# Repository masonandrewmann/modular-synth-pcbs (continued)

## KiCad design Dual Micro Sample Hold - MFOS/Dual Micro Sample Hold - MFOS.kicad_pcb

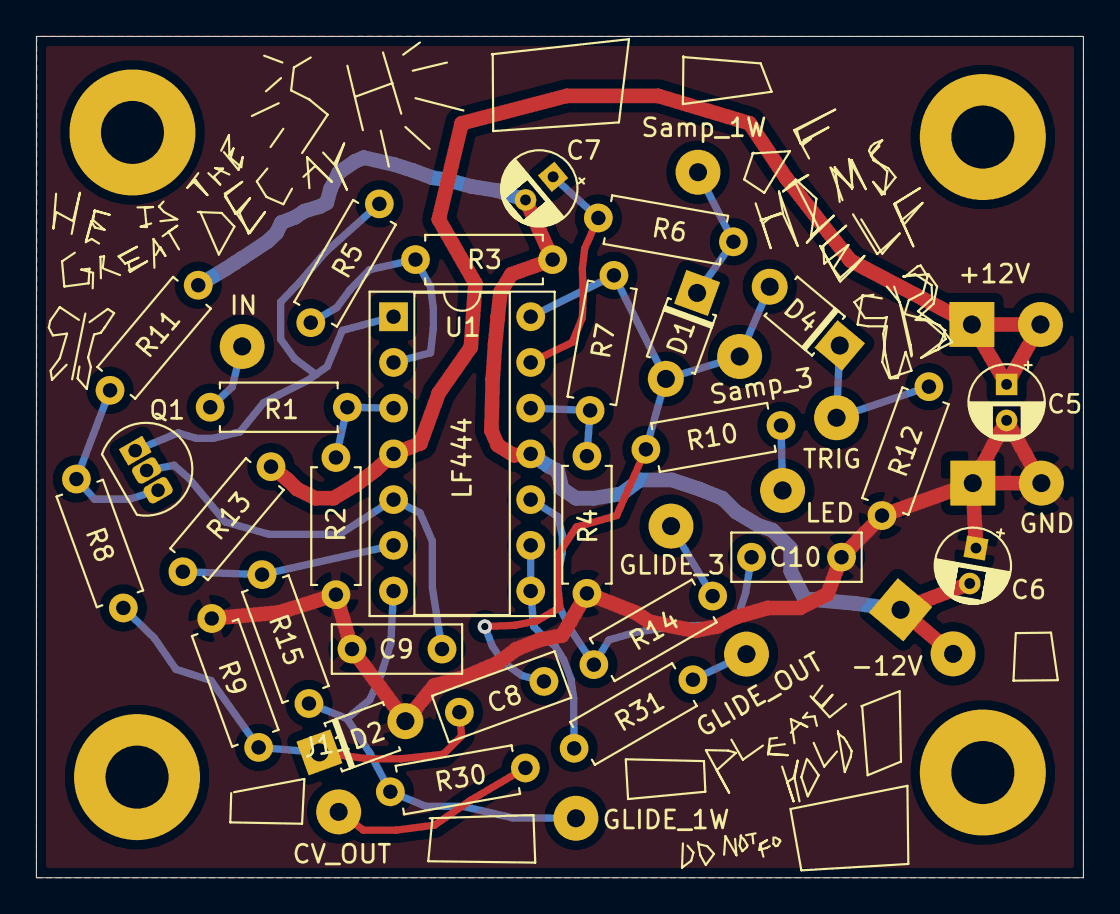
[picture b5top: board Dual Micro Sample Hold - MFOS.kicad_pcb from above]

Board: 2 copper layers, 58.2 x 46.7 mm, 40 parts (0 on the bottom side), 23 nets.

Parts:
C5, C6: 1u; CP_Radial_D4.0mm_P2.00mm
C7: 10u; CP_Radial_D4.0mm_P2.00mm
C8: 0.001u; C_Rect_L7.0mm_W2.5mm_P5.00mm
C9: 0.005u; C_Rect_L7.0mm_W2.5mm_P5.00mm
C10: 0.1u; C_Rect_L7.0mm_W2.5mm_P5.00mm
D1, D2, D4: 1N914; D_T-1_P5.08mm_Horizontal
J1: +12V_Conn; SolderWirePad_1x02_P3.81mm_Drill1mm
J2: GND_Conn; SolderWirePad_1x02_P3.81mm_Drill1mm
J3: -12V_Conn; SolderWirePad_1x02_P3.81mm_Drill1mm
J4: IN_A; SolderWirePad_1x01_Drill1mm
J5: SampRate_1W_A; SolderWirePad_1x01_Drill1mm
J6: SampRate_3_A; SolderWirePad_1x01_Drill1mm
J7: LED_A; SolderWirePad_1x01_Drill1mm
J8: Glide_1W_A; SolderWirePad_1x01_Drill1mm
J9: Glide_3_A; SolderWirePad_1x01_Drill1mm
J10: TRIG_A; SolderWirePad_1x01_Drill1mm
J11: CV_OUT_A; SolderWirePad_1x01_Drill1mm
J12: GLIDE_OUT_A; SolderWirePad_1x01_Drill1mm
Q1: Q_NJFET_DSG; TO-92L_Inline
R1, R2, R4, R8, R9: 100k; R_Axial_DIN0207_L6.3mm_D2.5mm_P7.62mm_Horizontal
R3: 560k; R_Axial_DIN0207_L6.3mm_D2.5mm_P7.62mm_Horizontal
R5: 200k; R_Axial_DIN0207_L6.3mm_D2.5mm_P7.62mm_Horizontal
R6: 4k7; R_Axial_DIN0207_L6.3mm_D2.5mm_P7.62mm_Horizontal
R7, R11: 470k; R_Axial_DIN0207_L6.3mm_D2.5mm_P7.62mm_Horizontal
R10: 10K; R_Axial_DIN0207_L6.3mm_D2.5mm_P7.62mm_Horizontal
R12: 100K; R_Axial_DIN0207_L6.3mm_D2.5mm_P7.62mm_Horizontal
R13: 150k; R_Axial_DIN0207_L6.3mm_D2.5mm_P7.62mm_Horizontal
R14: 220; R_Axial_DIN0207_L6.3mm_D2.5mm_P7.62mm_Horizontal
R15: 75k; R_Axial_DIN0207_L6.3mm_D2.5mm_P7.62mm_Horizontal
R30, R31: 1k; R_Axial_DIN0207_L6.3mm_D2.5mm_P7.62mm_Horizontal
U1: LF444; DIP-14_W7.62mm_Socket

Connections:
+12V: C5.1, J1.1, J1.2, R13.1, U1.4
-12V: C6.2, C7.2, J3.1, J3.2, R3.1, R11.2, U1.11
Earth: C5.2, C6.1, C9.2, C10.2, D2.2, J2.1, J2.2, R2.2, R4.1, R9.2, R12.2
unnamed: C7.1, R6.1, U1.13
unnamed: C8.1, D2.1, R8.1, R9.1
unnamed: C8.2, D1.2, D4.2, J6.1, R7.2, R10.1, U1.14
unnamed: C9.1, Q1.2, U1.5
unnamed: C10.1, R14.2, U1.10
unnamed: D1.1, J5.1, R6.2
unnamed: J7.1, R10.2
unnamed: D4.1, J10.1, R12.1
unnamed: J4.1, R1.1
unnamed: J8.1, R15.1, R30.1, U1.7
unnamed: J9.1, R14.1
unnamed: J11.1, R30.2
unnamed: J12.1, R31.2
unnamed: Q1.1, R5.2, U1.1
unnamed: Q1.3, R8.2, R11.1
unnamed: R1.2, R2.1, U1.3
unnamed: R3.2, R5.1, U1.2
unnamed: R4.2, R7.1, U1.12
unnamed: R13.2, R15.2, U1.6
unnamed: R31.1, U1.8, U1.9

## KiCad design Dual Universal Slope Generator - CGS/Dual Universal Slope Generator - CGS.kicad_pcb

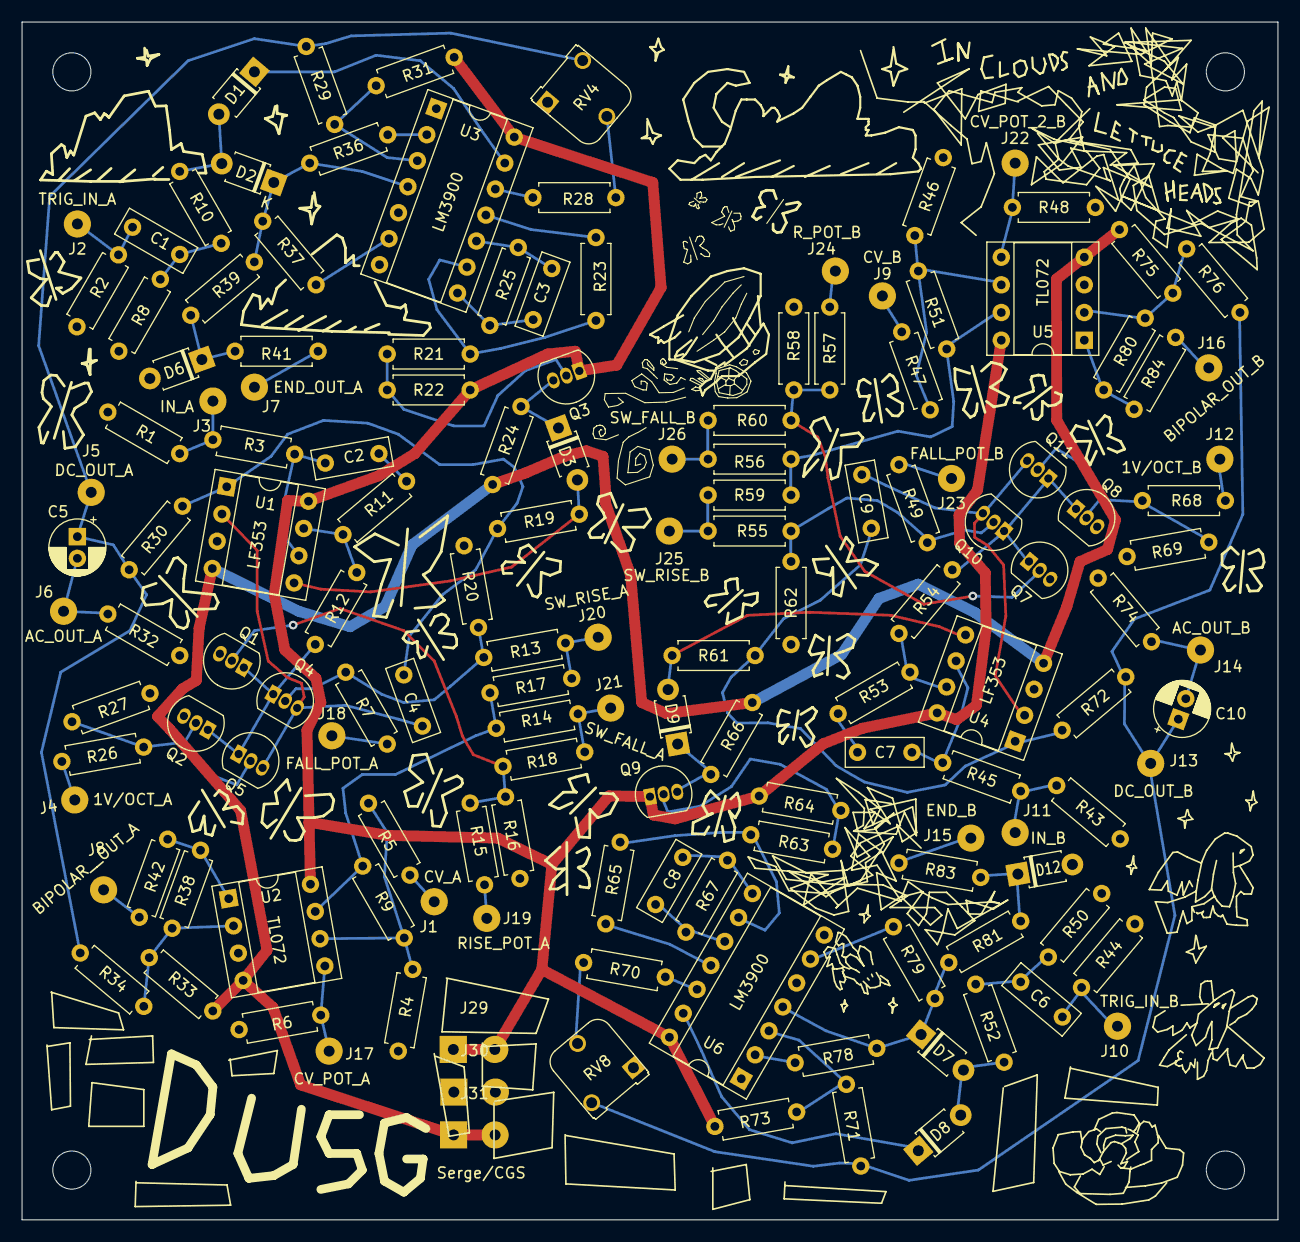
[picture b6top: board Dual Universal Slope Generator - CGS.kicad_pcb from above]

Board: 2 copper layers, 115.3 x 110.0 mm, 145 parts (0 on the bottom side), 89 nets.

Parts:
C1, C6: 1n; C_Rect_L7.0mm_W2.5mm_P5.00mm
C2, C3, C7, C8: 47p; C_Rect_L7.0mm_W2.5mm_P5.00mm
C4, C9: 22n; C_Rect_L7.0mm_W2.5mm_P5.00mm
C5, C10: 47uF; CP_Radial_D5.0mm_P2.00mm
D1, D2, D3, D7, D8, D9: 1N4148; D_T-1_P5.08mm_Horizontal
D6, D12: 5V6; D_T-1_P5.08mm_Horizontal
J1: CV_IN_A; SolderWirePad_1x01_Drill1mm
J2: TRIG_IN_A; SolderWirePad_1x01_Drill1mm
J3: IN_A; SolderWirePad_1x01_Drill1mm
J4: 1V/OCT_A; SolderWirePad_1x01_Drill1mm
J5: DC_OUT_A; SolderWirePad_1x01_Drill1mm
J6: AC_COUPLED_OUT_A; SolderWirePad_1x01_Drill1mm
J7: END_OUT_A; SolderWirePad_1x01_Drill1mm
J8: BIPOLAR_OUT_A; SolderWirePad_1x01_Drill1mm
J9: CV_IN_B; SolderWirePad_1x01_Drill1mm
J10: TRIG_IN_B; SolderWirePad_1x01_Drill1mm
J11: IN_B; SolderWirePad_1x01_Drill1mm
J12: 1V/OCT_B; SolderWirePad_1x01_Drill1mm
J13: DC_OUT_B; SolderWirePad_1x01_Drill1mm
J14: AC_COUPLED_OUT_B; SolderWirePad_1x01_Drill1mm
J15: END_OUT_B; SolderWirePad_1x01_Drill1mm
J16: BIPOLAR_OUT_B; SolderWirePad_1x01_Drill1mm
J17: CV_POT_A; SolderWirePad_1x01_Drill1mm
J18: FALL_POT_A; SolderWirePad_1x01_Drill1mm
J19: RISE_POT_A; SolderWirePad_1x01_Drill1mm
J20: SW_RISE_A; SolderWirePad_1x01_Drill1mm
J21: SW_FALL_A; SolderWirePad_1x01_Drill1mm
J22: CV_POT_2_B; SolderWirePad_1x01_Drill1mm
J23: FALL_POT_B; SolderWirePad_1x01_Drill1mm
J24: RISE_POT_B; SolderWirePad_1x01_Drill1mm
J25: SW_RISE_B; SolderWirePad_1x01_Drill1mm
J26: SW_FALL_B; SolderWirePad_1x01_Drill1mm
J29: +12V_Conn; SolderWirePad_1x02_P3.81mm_Drill1mm
J30: GND_Conn; SolderWirePad_1x02_P3.81mm_Drill1mm
J31: -12V_Conn; SolderWirePad_1x02_P3.81mm_Drill1mm
Q1, Q5, Q7, Q11: 2N3904; TO-92_Inline
Q2, Q3, Q4, Q8, Q9, Q10: 2N3906; TO-92_Inline
R1, R2, R3, R8, R34, R38, R43, R44, R45, R50, R76, R80: 100K; R_Axial_DIN0207_L6.3mm_D2.5mm_P7.62mm_Horizontal
R4, R6, R32, R36, R37, R46, R48, R74, R78, R79: 1M; R_Axial_DIN0207_L6.3mm_D2.5mm_P7.62mm_Horizontal
R5, R33, R47, R75: 470K; R_Axial_DIN0207_L6.3mm_D2.5mm_P7.62mm_Horizontal
R7, R15, R26, R49, R57, R68: 82K; R_Axial_DIN0207_L6.3mm_D2.5mm_P7.62mm_Horizontal
R9, R23, R25, R51, R65, R67: 820K; R_Axial_DIN0207_L6.3mm_D2.5mm_P7.62mm_Horizontal
R10, R13, R14, R52, R55, R56: 33K; R_Axial_DIN0207_L6.3mm_D2.5mm_P7.62mm_Horizontal
R11, R31, R53, R73: 10M; R_Axial_DIN0207_L6.3mm_D2.5mm_P7.62mm_Horizontal
R12, R54: 8K2; R_Axial_DIN0207_L6.3mm_D2.5mm_P7.62mm_Horizontal
R16, R20, R39, R58, R62, R81: 2K2; R_Axial_DIN0207_L6.3mm_D2.5mm_P7.62mm_Horizontal
R17, R18, R59, R60: 47K; R_Axial_DIN0207_L6.3mm_D2.5mm_P7.62mm_Horizontal
R19, R21, R24, R28, R61, R63, R66, R70: 220K; R_Axial_DIN0207_L6.3mm_D2.5mm_P7.62mm_Horizontal
R22, R64: 68K; R_Axial_DIN0207_L6.3mm_D2.5mm_P7.62mm_Horizontal
R27, R69: 1K5; R_Axial_DIN0207_L6.3mm_D2.5mm_P7.62mm_Horizontal
R29, R71: 330K; R_Axial_DIN0207_L6.3mm_D2.5mm_P7.62mm_Horizontal
R30, R72: 100; R_Axial_DIN0207_L6.3mm_D2.5mm_P7.62mm_Horizontal
R41, R83: 1K; R_Axial_DIN0207_L6.3mm_D2.5mm_P7.62mm_Horizontal
R42, R84: 330; R_Axial_DIN0207_L6.3mm_D2.5mm_P7.62mm_Horizontal
RV4, RV8: 100K; Potentiometer_Runtron_RM-065_Vertical
U1, U4: LF353; DIP-8_W7.62mm_Socket
U2, U5: TL072; DIP-8_W7.62mm_Socket
U3, U6: LM3900; DIP-14_W7.62mm_Socket

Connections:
+12V: J29.1, J29.2, Q3.1, Q9.1, R22.2, R31.2, R64.2, R73.2, U1.8, U2.8, U3.14, U4.8, U5.8, U6.14
-12V: J31.1, J31.2, R24.1, R33.2, R66.1, R75.2, U1.4, U2.4, U4.4, U5.4
Earth: D6.2, D12.2, J30.1, J30.2, Q1.3, Q2.3, Q7.3, Q8.3, R1.2, R2.2, R4.1, R6.2, R8.2, R16.2, R20.2, R27.2, R32.1, R43.2, R44.2, R46.1, R48.2, R50.2, R58.2, R62.2, R69.2, R74.1, RV4.1, RV8.1, U1.3, U2.3, U3.1, U3.7, U4.3, U5.3, U6.1, U6.7
unnamed: C1.1, R8.1, R10.2
unnamed: C1.2, J2.1, R2.1
unnamed: C2.1, R11.1
unnamed: C2.2, R3.2, U1.6
unnamed: C3.1, R25.1, U3.10
unnamed: C3.2, R25.2, U3.8
unnamed: C4.1, R19.1, R30.1, U1.1
unnamed: C4.2, Q4.3, Q5.3, U1.2
unnamed: C5.1, J5.1, R29.2, R30.2, R34.2, RV4.3
unnamed: C5.2, J6.1, R32.2
unnamed: C6.1, R50.1, R52.2
unnamed: C6.2, J10.1, R44.1
unnamed: C7.1, R53.1
unnamed: C7.2, R45.2, U4.6
unnamed: C8.1, R67.1, U6.10
unnamed: C8.2, R67.2, U6.8
unnamed: C9.1, R61.1, R72.1, U4.1
unnamed: C9.2, Q10.3, Q11.3, U4.2
unnamed: C10.1, J13.1, R71.2, R72.2, R76.2, RV8.3
unnamed: C10.2, J14.1, R74.2
unnamed: D1.1, U3.13
unnamed: D1.2, D2.2, R10.1
unnamed: D2.1, R36.1, R37.1, R39.2, U3.4
unnamed: D3.1, Q3.3, R24.2
unnamed: D3.2, R19.2, U1.5
unnamed: D6.1, R39.1, R41.2
unnamed: D7.1, R78.1, R79.1, R81.2, U6.4
unnamed: D7.2, D8.2, R52.1
unnamed: D8.1, U6.13
unnamed: D9.1, Q9.3, R66.2
unnamed: D9.2, R61.2, U4.5
unnamed: D12.1, R81.1, R83.2
unnamed: J1.1, R5.1
unnamed: J3.1, R1.1, R3.1
unnamed: J4.1, R26.2
unnamed: J7.1, R41.1
unnamed: J8.1, R42.1
unnamed: J9.1, R47.1
unnamed: J11.1, R43.1, R45.1
unnamed: J12.1, R68.2
unnamed: J15.1, R83.1
unnamed: J16.1, R84.1
unnamed: J17.1, R6.1, U2.5
unnamed: J18.1, R7.1
unnamed: J19.1, R15.1
unnamed: J20.1, R13.2, R17.1
unnamed: J21.1, R14.2, R18.1
unnamed: J22.1, R48.1, U5.5
unnamed: J23.1, R49.1
unnamed: J24.1, R57.1
unnamed: J25.1, R55.2, R59.1
unnamed: J26.1, R56.2, R60.1
unnamed: Q1.1, Q2.1, Q4.1, Q5.1, R12.2
unnamed: Q1.2, R15.2, R16.1, R18.2
unnamed: Q2.2, Q5.2, R26.1, R27.1
unnamed: Q3.2, R21.1, R22.1
unnamed: Q4.2, R7.2, R17.2, R20.1
unnamed: Q7.2, R57.2, R58.1, R60.2
unnamed: Q9.2, R63.1, R64.1
unnamed: Q7.1, Q8.1, Q10.1, Q11.1, R54.2
unnamed: Q10.2, R49.2, R59.2, R62.1
unnamed: Q8.2, Q11.2, R68.1, R69.1
unnamed: R4.2, R5.2, R9.1, U2.6
unnamed: R11.2, R12.1, U1.7
unnamed: R9.2, R13.1, R14.1, U2.7
unnamed: R21.2, R23.2, U3.9
unnamed: R23.1, U3.11
unnamed: R28.1, RV4.2
unnamed: R28.2, U3.12
unnamed: R29.1, R31.1, U3.3
unnamed: R33.1, R34.1, R38.2, U2.2
unnamed: R36.2, U3.2
unnamed: R37.2, U3.6
unnamed: R38.1, R42.2, U2.1
unnamed: R46.2, R47.2, R51.1, U5.6
unnamed: R51.2, R55.1, R56.1, U5.7
unnamed: R53.2, R54.1, U4.7
unnamed: R63.2, R65.2, U6.9
unnamed: R65.1, U6.11
unnamed: R70.1, RV8.2
unnamed: R70.2, U6.12
unnamed: R71.1, R73.1, U6.3
unnamed: R75.1, R76.1, R80.2, U5.2
unnamed: R78.2, U6.2
unnamed: R79.2, U6.6
unnamed: R80.1, R84.2, U5.1

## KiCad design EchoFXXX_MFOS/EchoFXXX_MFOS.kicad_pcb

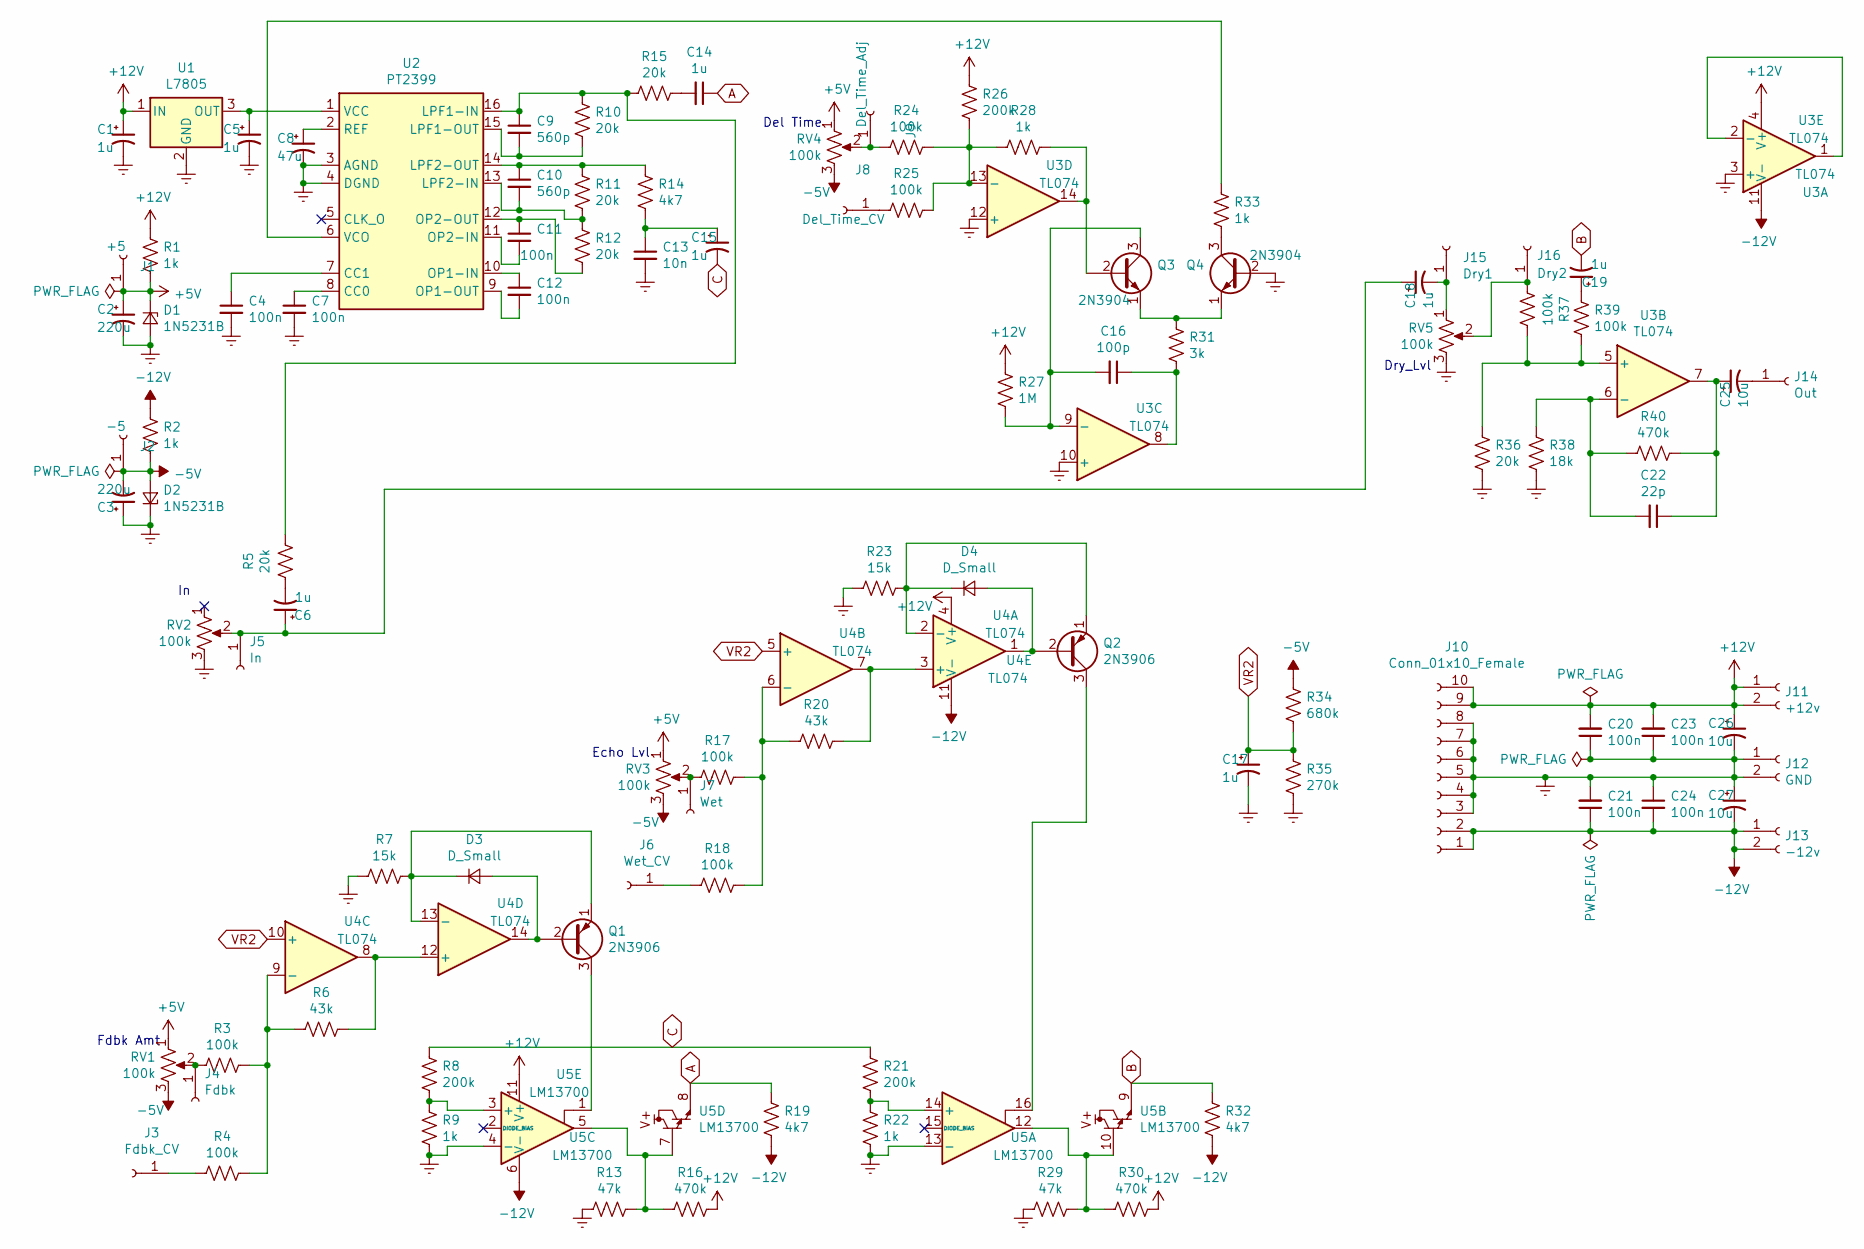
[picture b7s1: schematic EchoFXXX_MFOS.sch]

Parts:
C1, C5, C6, C14, C15, C17, C18, C19: 1u; CP_Radial_D5.0mm_P2.50mm
C2, C3: 220u; CP_Radial_D5.0mm_P2.50mm
C4, C7, C11, C12, C20, C21, C23, C24: 100n; C_Rect_L7.0mm_W2.5mm_P5.00mm
C8: 47u; CP_Radial_D5.0mm_P2.50mm
C9, C10: 560p; C_Rect_L7.0mm_W2.5mm_P5.00mm
C13: 10n; C_Rect_L7.0mm_W2.5mm_P5.00mm
C16: 100p; C_Rect_L7.0mm_W2.5mm_P5.00mm
C22: 22p; C_Rect_L7.0mm_W2.5mm_P5.00mm
C25, C26, C27: 10u; CP_Radial_D5.0mm_P2.50mm
D1, D2: 1N5231B; D_T-1_P5.08mm_Horizontal
D3, D4: D_Small; D_T-1_P5.08mm_Horizontal
J1: +5; SolderWirePad_1x01_Drill1mm
J2: -5; SolderWirePad_1x01_Drill1mm
J3: Fdbk_CV; SolderWirePad_1x01_Drill1mm
J4: Fdbk; SolderWirePad_1x01_Drill1mm
J5: In; SolderWirePad_1x01_Drill1mm
J6: Wet_CV; SolderWirePad_1x01_Drill1mm
J7: Wet; SolderWirePad_1x01_Drill1mm
J8: Del_Time_CV; SolderWirePad_1x01_Drill1mm
J9: Del_Time_Adj; SolderWirePad_1x01_Drill1mm
J10: Conn_01x10_Female; IDC-Header_2x05_P2.54mm_Vertical
J11: +12v; SolderWirePad_1x02_P3.81mm_Drill1mm
J12: GND; SolderWirePad_1x02_P3.81mm_Drill1mm
J13: -12v; SolderWirePad_1x02_P3.81mm_Drill1mm
J14: Out; SolderWirePad_1x01_Drill1mm
J15: Dry1; SolderWirePad_1x01_Drill1mm
J16: Dry2; SolderWirePad_1x01_Drill1mm
Q1, Q2: 2N3906; TO-92_Inline_Wide
Q3, Q4: 2N3904; TO-92_Inline_Wide
R1, R2, R9, R22, R28, R33: 1k; R_Axial_DIN0207_L6.3mm_D2.5mm_P7.62mm_Horizontal
R3, R4, R17, R18, R24, R25, R37, R39: 100k; R_Axial_DIN0207_L6.3mm_D2.5mm_P7.62mm_Horizontal
R5, R10, R11, R12, R15, R36: 20k; R_Axial_DIN0207_L6.3mm_D2.5mm_P7.62mm_Horizontal
R6, R20: 43k; R_Axial_DIN0207_L6.3mm_D2.5mm_P7.62mm_Horizontal
R7, R23: 15k; R_Axial_DIN0207_L6.3mm_D2.5mm_P7.62mm_Horizontal
R8, R21, R26: 200k; R_Axial_DIN0207_L6.3mm_D2.5mm_P7.62mm_Horizontal
R13, R29: 47k; R_Axial_DIN0207_L6.3mm_D2.5mm_P7.62mm_Horizontal
R14, R19, R32: 4k7; R_Axial_DIN0207_L6.3mm_D2.5mm_P7.62mm_Horizontal
R16, R30, R40: 470k; R_Axial_DIN0207_L6.3mm_D2.5mm_P7.62mm_Horizontal
R27: 1M; R_Axial_DIN0207_L6.3mm_D2.5mm_P7.62mm_Horizontal
R31: 3k; R_Axial_DIN0207_L6.3mm_D2.5mm_P7.62mm_Horizontal
R34: 680k; R_Axial_DIN0207_L6.3mm_D2.5mm_P7.62mm_Horizontal
R35: 270k; R_Axial_DIN0207_L6.3mm_D2.5mm_P7.62mm_Horizontal
R38: 18k; R_Axial_DIN0207_L6.3mm_D2.5mm_P7.62mm_Horizontal
RV1, RV2, RV3, RV4, RV5: 100k
U1: L7805; TO-220-3_Vertical
U2: PT2399; DIP-16_W7.62mm_Socket
U3, U4: TL074; DIP-14_W7.62mm_Socket
U5: LM13700; DIP-16_W7.62mm_Socket

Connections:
+5V: C2.1, D1.1 (K), J1.1, R1.2, RV1.1, RV3.1, RV4.1
+12V: C1.1, C20.2, C23.2, C26.1, J10.9, J10.10, J11.1, J11.2, R1.1, R16.1, R26.2, R27.2, R30.1, U1.1 (IN), U3.4 (V+), U4.4 (V+), U5.11 (V+)
-5V: C3.2, D2.2 (A), J2.1, R2.2, R34.1, RV1.3, RV3.3, RV4.3
-12V: C21.1, C24.2, C27.2, J10.1, J10.2, J13.1, J13.2, R2.1, R19.1, R32.1, U3.11 (V-), U4.11 (V-), U5.6 (V-)
A: C14.1, R19.2, U5.8
B: C19.2, R32.2, U5.9
C: C15.2, R8.1, R21.1
Earth: C1.2, C2.2, C3.1, C4.2, C5.2, C7.2, C8.2, C13.2, C17.2, C20.1, C21.2, C23.1, C24.1, C26.2, C27.1, D1.2 (A), D2.1 (K), J10.3, J10.4, J10.5, J10.6, J10.7, J10.8, J12.1, J12.2, Q4.2 (B), R7.1, R9.2, R13.2, R22.2, R23.1, R29.2, R35.2, R36.2, R38.2, RV2.3, RV5.3, U1.2 (GND), U2.3 (AGND), U2.4 (DGND), U3.3 (+), U3.10 (+), U3.12 (+), U5.4 (-), U5.13 (-)
unnamed: C4.1, U2.7 (CC1)
unnamed: C5.1, U1.3 (OUT), U2.1 (VCC)
unnamed: C6.2, R5.1
unnamed: C7.1, U2.8 (CC0)
unnamed: C8.1, U2.2 (REF)
unnamed: C9.1, R5.2, R10.1, R15.2, U2.16 (LPF1-IN)
unnamed: C9.2, R10.2, U2.15 (LPF1-OUT)
unnamed: C10.1, R11.1, R14.1, U2.14 (LPF2-OUT)
unnamed: C10.2, R11.2, R12.1, U2.13 (LPF2-IN)
unnamed: C11.1, R12.2, U2.12 (OP2-OUT)
unnamed: C11.2, U2.11 (OP2-IN)
unnamed: C12.1, U2.10 (OP1-IN)
unnamed: C12.2, U2.9 (OP1-OUT)
unnamed: C13.1, C15.1, R14.2
unnamed: C14.2, R15.1
unnamed: C16.1, R31.1, U3.8
unnamed: C16.2, Q3.3 (C), R27.1, U3.9 (-)
unnamed: C6.1, C18.1, J5.1, RV2.2
unnamed: C18.2, J15.1, RV5.1
unnamed: C19.1, R39.1
unnamed: C22.1, C25.1, R40.2, U3.7
unnamed: C22.2, R38.1, R40.1, U3.6 (-)
unnamed: C25.2, J14.1
unnamed: D3.1 (K), Q1.1 (E), R7.2, U4.13 (-)
unnamed: D3.2 (A), Q1.2 (B), U4.14
unnamed: D4.1 (K), Q2.1 (E), R23.2, U4.2 (-)
unnamed: D4.2 (A), Q2.2 (B), U4.1
unnamed: J3.1, R4.1
unnamed: J4.1, R3.1, RV1.2
unnamed: J6.1, R18.1
unnamed: J7.1, R17.1, RV3.2
unnamed: J8.1, R25.2
unnamed: J9.1, R24.2, RV4.2
unnamed: J16.1, R37.2, RV5.2
unnamed: Q1.3 (C), U5.1
unnamed: Q2.3 (C), U5.16
unnamed: Q3.1 (E), Q4.1 (E), R31.2
unnamed: Q3.2 (B), R28.1, U3.14
unnamed: Q4.3 (C), R33.1
unnamed: R3.2, R4.2, R6.1, U4.9 (-)
unnamed: R6.2, U4.8, U4.12 (+)
unnamed: R8.2, R9.1, U5.3 (+)
unnamed: R13.1, R16.2, U5.5, U5.7
unnamed: R17.2, R18.2, R20.1, U4.6 (-)
unnamed: R20.2, U4.3 (+), U4.7
unnamed: R21.2, R22.1, U5.14 (+)
unnamed: R24.1, R25.1, R26.1, R28.2, U3.13 (-)
unnamed: R29.1, R30.2, U5.10, U5.12
unnamed: R33.2, U2.6 (VCO)
unnamed: R36.1, R37.1, R39.2, U3.5 (+)
unnamed: U3.1, U3.2 (-)
VR2: C17.1, R34.2, R35.1, U4.5 (+), U4.10 (+)

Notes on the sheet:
Del Time
Dry_Lvl
Fdbk Amt
Echo Lvl

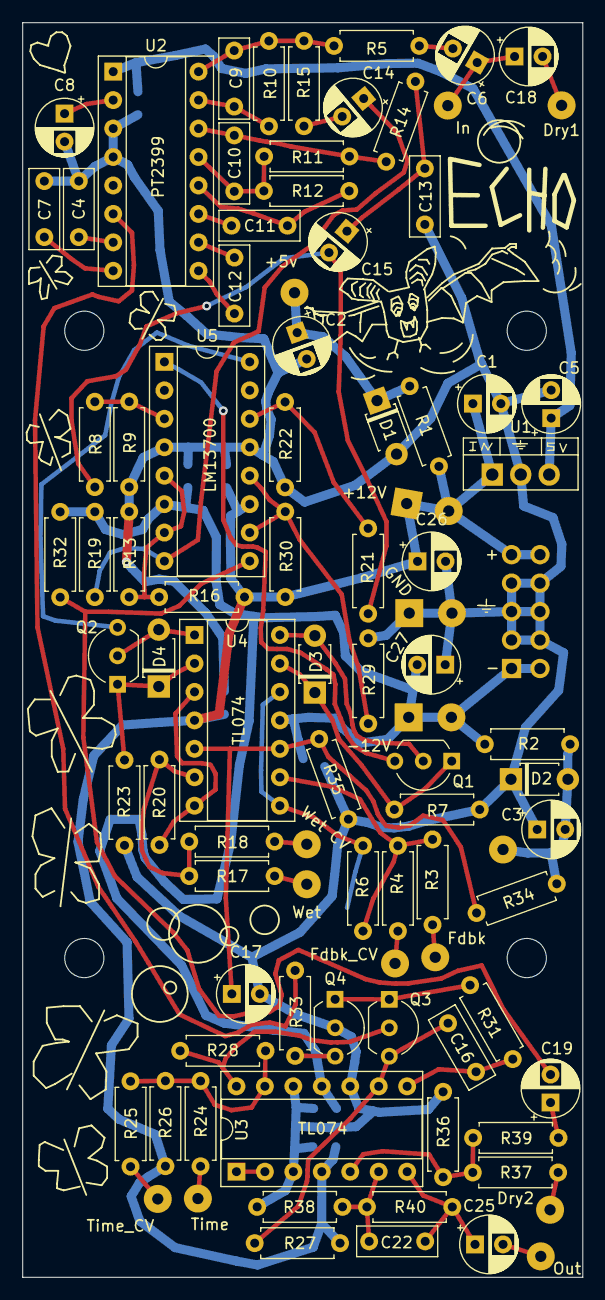
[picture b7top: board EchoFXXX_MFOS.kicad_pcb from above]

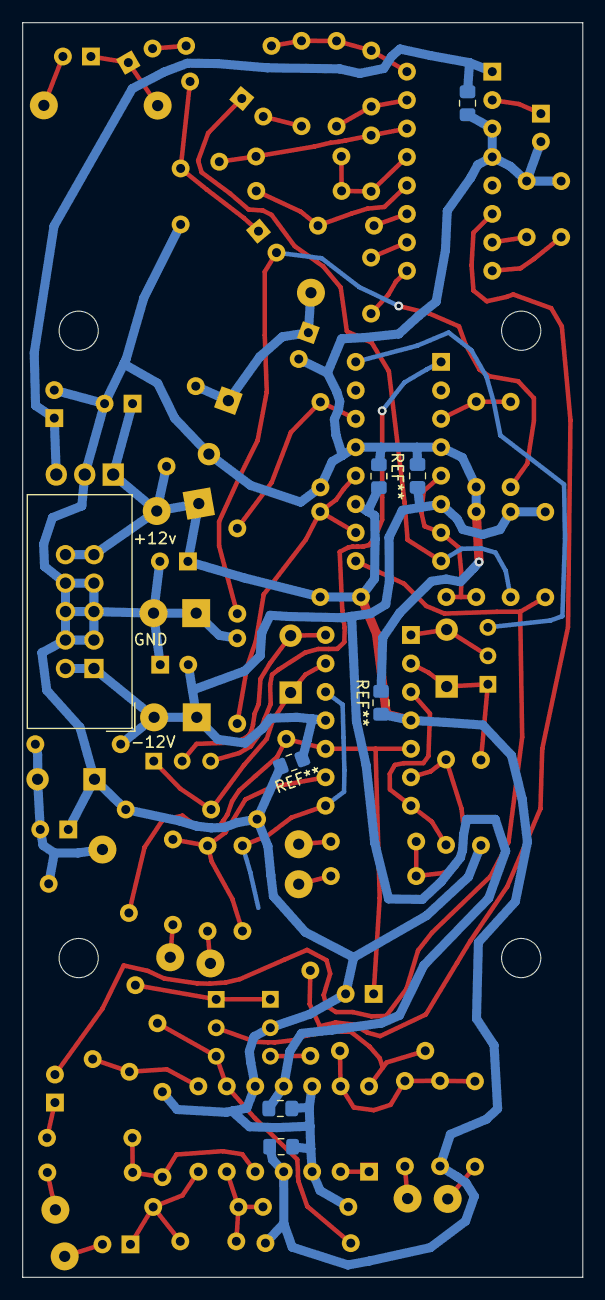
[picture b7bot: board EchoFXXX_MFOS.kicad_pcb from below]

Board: 2 copper layers, 50.0 x 112.0 mm, 92 parts (4 on the bottom side), 60 nets.

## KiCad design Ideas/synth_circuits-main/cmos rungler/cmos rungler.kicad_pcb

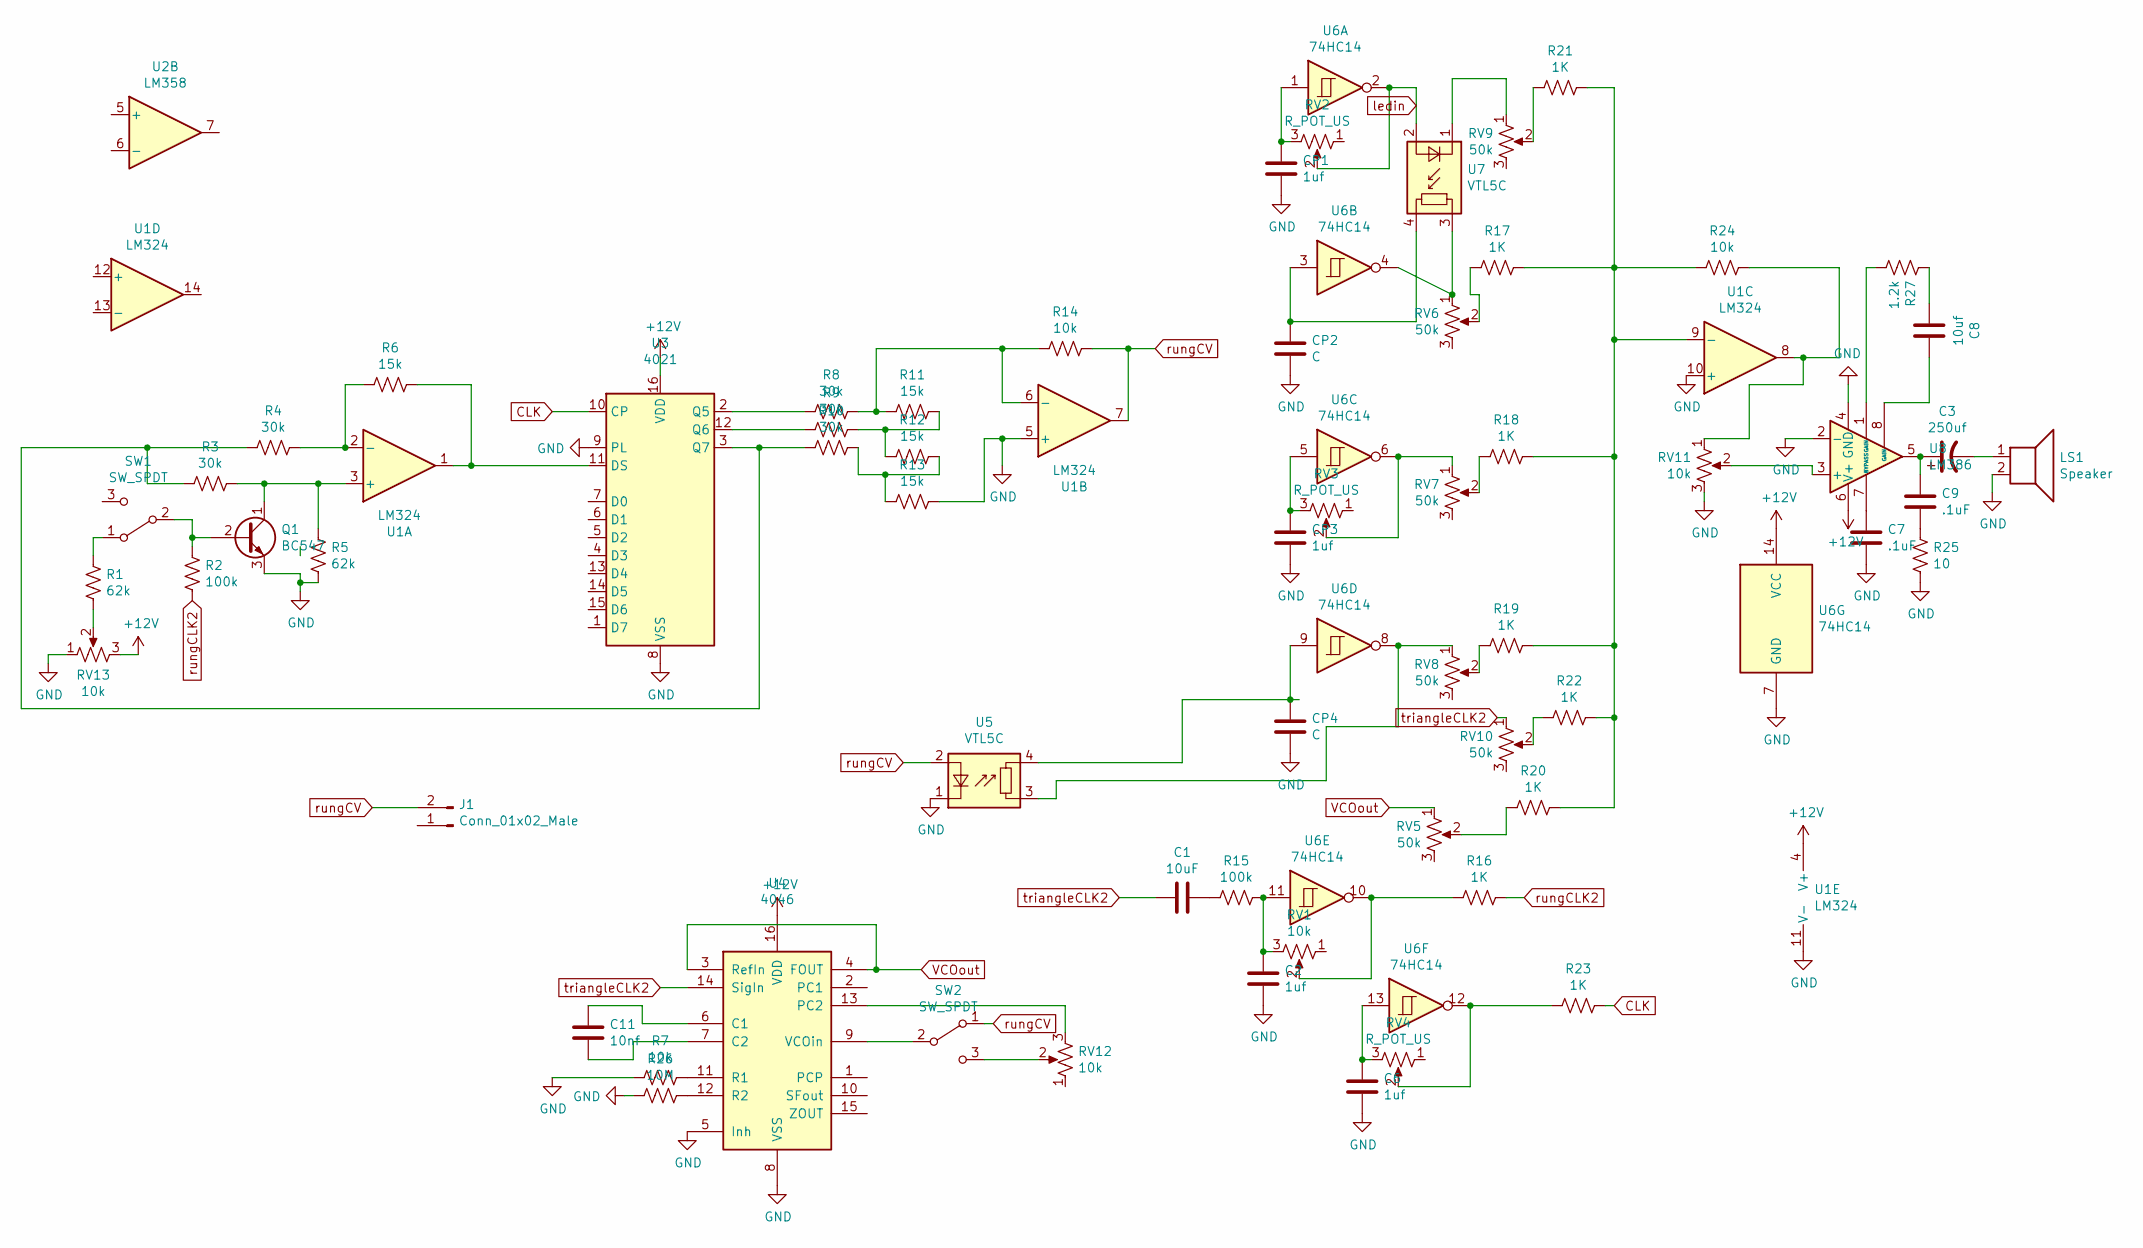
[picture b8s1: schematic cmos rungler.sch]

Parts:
C1: 10uF; CP_Radial_D14.0mm_P7.50mm
C2, C6: 1uf; CP_Radial_D10.0mm_P5.00mm
C3: 250uf; CP_Radial_D14.0mm_P7.50mm
C7, C9: .1uF; CP_Radial_D10.0mm_P5.00mm
C8: 10uf; CP_Radial_D10.0mm_P5.00mm
C11: 10nf; CP_Radial_D10.0mm_P5.00mm
CP1, CP3: 1uf; CP_Radial_D10.0mm_P5.00mm
CP2, CP4: C; CP_Radial_D10.0mm_P5.00mm
J1: Conn_01x02_Male; PinHeader_1x02_P2.54mm_Vertical
LS1: Speaker; PinHeader_1x02_P2.54mm_Vertical
Q1: BC547; TO-92_Inline
R1, R5: 62k; R_Axial_DIN0411_L9.9mm_D3.6mm_P15.24mm_Horizontal
R2, R15: 100k; R_Axial_DIN0411_L9.9mm_D3.6mm_P15.24mm_Horizontal
R3, R4, R8, R9, R10: 30k; R_Axial_DIN0411_L9.9mm_D3.6mm_P15.24mm_Horizontal
R6, R11, R12, R13: 15k; R_Axial_DIN0411_L9.9mm_D3.6mm_P15.24mm_Horizontal
R7, R14, R24: 10k; R_Axial_DIN0411_L9.9mm_D3.6mm_P15.24mm_Horizontal
R16, R17, R18, R19, R20, R21, R22, R23: 1K; R_Axial_DIN0411_L9.9mm_D3.6mm_P15.24mm_Horizontal
R25: 10; R_Axial_DIN0411_L9.9mm_D3.6mm_P15.24mm_Horizontal
R26: 10M; R_Axial_DIN0411_L9.9mm_D3.6mm_P15.24mm_Horizontal
R27: 1.2k; R_Axial_DIN0411_L9.9mm_D3.6mm_P15.24mm_Horizontal
RV1, RV11, RV12, RV13: 10k; SolderWirePad_1x03_P5.715mm_Drill2mm
RV2, RV3, RV4: R_POT_US; SolderWirePad_1x03_P5.715mm_Drill2mm
RV5, RV6, RV7, RV8, RV9, RV10: 50k; SolderWirePad_1x03_P5.715mm_Drill2mm
SW1, SW2: SW_SPDT; SolderWirePad_1x03_P5.715mm_Drill2mm
U1: LM324; DIP-14_W7.62mm_Socket_LongPads
U2: LM358; DIP-8_W7.62mm_Socket_LongPads
U3: 4021; DIP-16_W7.62mm_Socket_LongPads
U4: 4046; DIP-16_W7.62mm_Socket_LongPads
U5, U7: VTL5C; PerkinElmer_VTL5C
U6: 74HC14; DIP-14_W7.62mm_Socket_LongPads
U8: LM386; DIP-8_W7.62mm_Socket_LongPads

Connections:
+12V: RV13.3, U1.4 (V+), U3.16 (VDD), U4.16 (VDD), U6.14 (VCC), U8.6 (V+)
CLK: R23.1, U3.10 (CP)
GND: C2.2, C6.2, C7.2, CP1.2, CP2.2, CP3.2, CP4.2, LS1.2, Q1.3 (E), R5.1, R7.2, R13.1, R25.1, R26.1, RV11.3, RV13.1, U1.5 (+), U1.10 (+), U1.11 (V-), U3.8 (VSS), U3.9 (PL), U4.5 (Inh), U4.8 (VSS), U5.1 (-), U6.7 (GND), U8.2 (-), U8.4 (GND)
unnamed: C1.2, R15.2
unnamed: C2.1, R15.1, RV1.3, U6.11
unnamed: C3.1, C9.1, U8.5
unnamed: C3.2, LS1.1
unnamed: C6.1, RV4.3, U6.13
unnamed: C7.1, U8.7 (BYPASS)
unnamed: C8.1, U8.8 (GAIN)
unnamed: C8.2, R27.2
unnamed: C9.2, R25.2
unnamed: C11.1, U4.6 (C1)
unnamed: C11.2, U4.7 (C2)
unnamed: CP1.1, RV2.3, U6.1
unnamed: CP2.1, U6.3, U7.4
unnamed: CP3.1, RV3.3, U6.5
unnamed: CP4.1, U5.4, U6.9
unnamed: Q1.1 (C), R3.1, R5.2, U1.3 (+)
unnamed: Q1.2 (B), R2.2, SW1.2 (B)
unnamed: R1.1, RV13.2
unnamed: R1.2, SW1.1 (A)
unnamed: R4.1, R6.2, U1.2 (-)
unnamed: R6.1, U1.1, U3.11 (DS)
unnamed: R7.1, U4.11 (R1)
unnamed: R8.2, U3.2 (Q5)
unnamed: R9.2, U3.12 (Q6)
unnamed: R10.1, R12.1, R13.2
unnamed: R3.2, R4.2, R10.2, U3.3 (Q7)
unnamed: R9.1, R11.1, R12.2
unnamed: R8.1, R11.2, R14.2, U1.6 (-)
unnamed: R16.2, RV1.2, U6.10
unnamed: R17.1, R18.1, R19.1, R20.1, R21.1, R22.1, R24.2, U1.9 (-)
unnamed: R17.2, RV6.2
unnamed: R18.2, RV7.2
unnamed: R19.2, RV8.2
unnamed: R20.2, RV5.2
unnamed: R21.2, RV9.2
unnamed: R22.2, RV10.2
unnamed: R23.2, RV4.2, U6.12
unnamed: R24.1, RV11.1, U1.8
unnamed: R26.2, U4.12 (R2)
unnamed: R27.1, U8.1 (GAIN)
unnamed: RV3.2, RV7.1, U6.6
unnamed: RV6.1, U6.4, U7.3
unnamed: RV8.1, U5.3, U6.8
unnamed: RV9.1, U7.1 (-)
unnamed: RV11.2, U8.3 (+)
unnamed: RV12.2, SW2.3 (C)
unnamed: RV12.3, U4.13 (PC2)
unnamed: SW2.2 (B), U4.9 (VCOin)
VCOout: RV5.1, U4.3 (RefIn), U4.4 (FOUT)
ledin: RV2.2, U6.2, U7.2 (+)
rungCLK2: R2.1, R16.1
rungCV: J1.2, R14.1, SW2.1 (A), U1.7, U5.2 (+)
triangleCLK2: C1.1, RV10.1, U4.14 (SigIn)

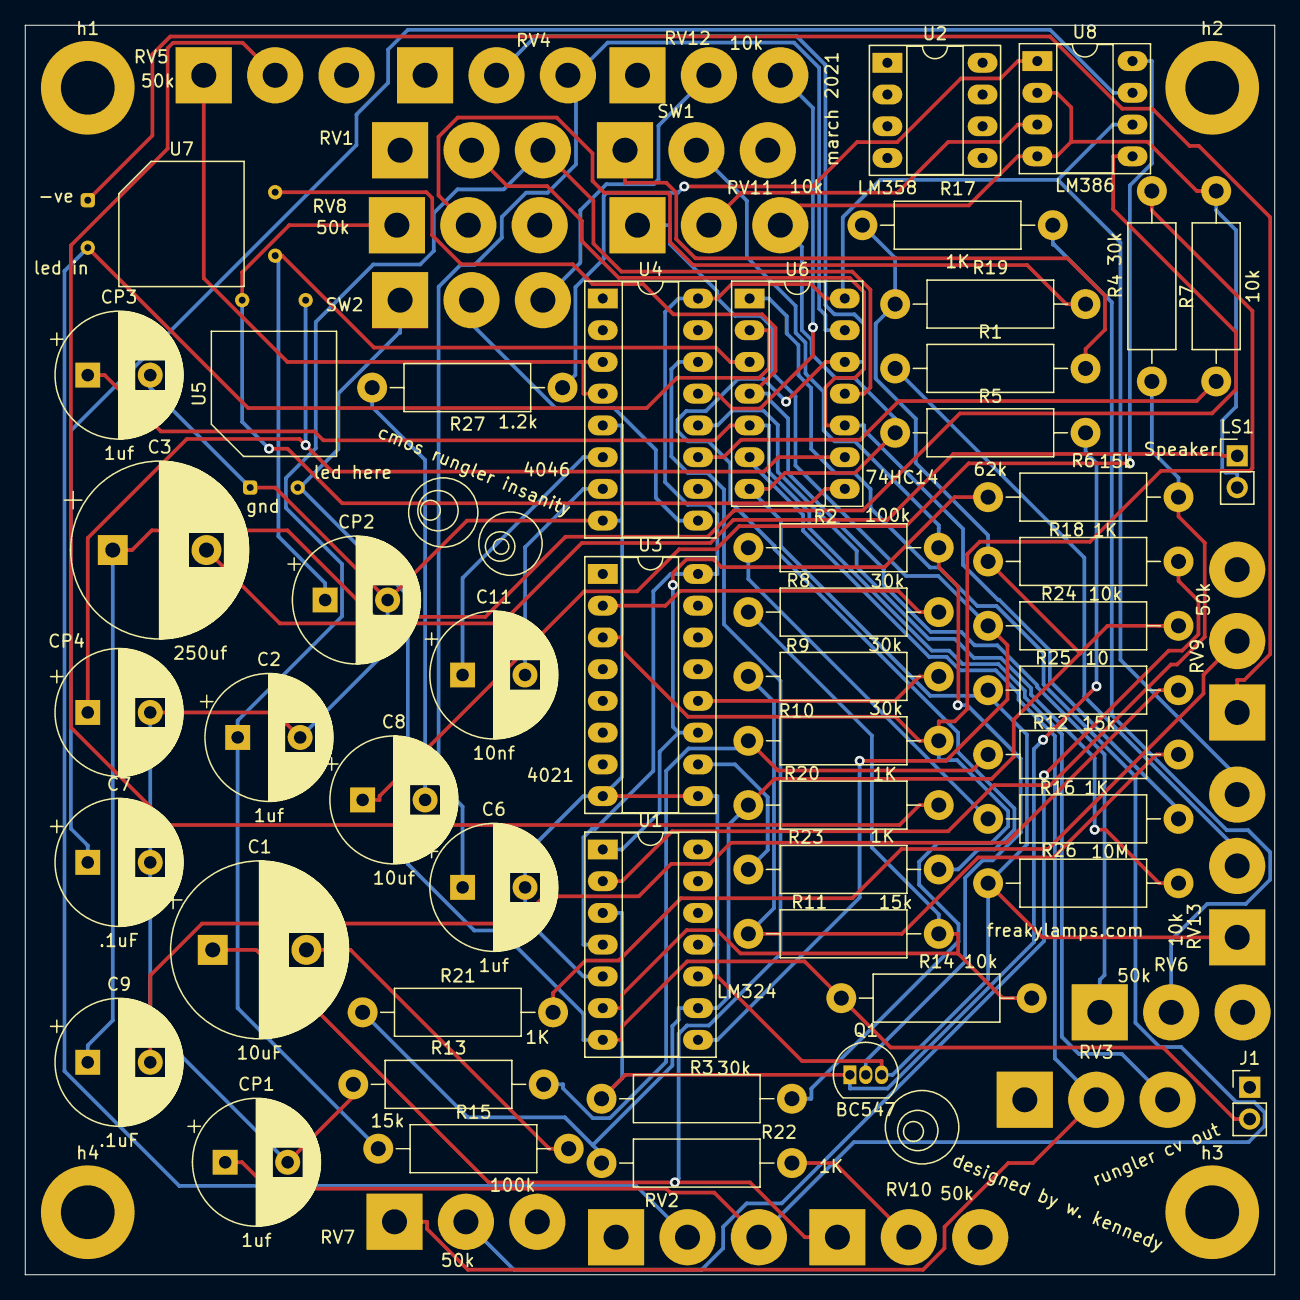
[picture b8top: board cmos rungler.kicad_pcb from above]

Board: 2 copper layers, 100.0 x 100.0 mm, 69 parts (0 on the bottom side), 56 nets.

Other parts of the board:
h1, h2, h3, h4: MountingHole_4.3mm_M4_DIN965_Pad

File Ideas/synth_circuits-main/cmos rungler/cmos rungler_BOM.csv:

"Id";"Designator";"Package";"Quantity";"Designation";"Supplier and ref";
1;"h4,h3,h2,h1";"MountingHole_4.3mm_M4_DIN965_Pad";4;"MountingHole_4.3mm_M4_DIN965_Pad";;;
2;"U8";"DIP-8_W7.62mm_Socket_LongPads";1;"LM386";;;
3;"U7,U5";"PerkinElmer_VTL5C";2;"VTL5C";;;
4;"U6";"DIP-14_W7.62mm_Socket_LongPads";1;"74HC14";;;
5;"U4";"DIP-16_W7.62mm_Socket_LongPads";1;"4046";;;
6;"U3";"DIP-16_W7.62mm_Socket_LongPads";1;"4021";;;
7;"U2";"DIP-8_W7.62mm_Socket_LongPads";1;"LM358";;;
8;"U1";"DIP-14_W7.62mm_Socket_LongPads";1;"LM324";;;
9;"SW2,SW1";"SolderWirePad_1x03_P5.715mm_Drill2mm";2;"SW_SPDT";;;
10;"RV13,RV12,RV11,RV1";"SolderWirePad_1x03_P5.715mm_Drill2mm";4;"10k";;;
11;"RV10,RV9,RV8,RV7,RV6,RV5";"SolderWirePad_1x03_P5.715mm_Drill2mm";6;"50k";;;
12;"RV4,RV3,RV2";"SolderWirePad_1x03_P5.715mm_Drill2mm";3;"R_POT_US";;;
13;"R27";"R_Axial_DIN0411_L9.9mm_D3.6mm_P15.24mm_Horizontal";1;"1.2k";;;
14;"R26";"R_Axial_DIN0411_L9.9mm_D3.6mm_P15.24mm_Horizontal";1;"10M";;;
15;"R25";"R_Axial_DIN0411_L9.9mm_D3.6mm_P15.24mm_Horizontal";1;"10";;;
16;"R24,R14,R7";"R_Axial_DIN0411_L9.9mm_D3.6mm_P15.24mm_Horizontal";3;"10k";;;
17;"R23,R22,R21,R20,R19,R18,R17,R16";"R_Axial_DIN0411_L9.9mm_D3.6mm_P15.24mm_Horizontal";8;"1K";;;
18;"R15,R2";"R_Axial_DIN0411_L9.9mm_D3.6mm_P15.24mm_Horizontal";2;"100k";;;
19;"R13,R12,R11,R6";"R_Axial_DIN0411_L9.9mm_D3.6mm_P15.24mm_Horizontal";4;"15k";;;
20;"R10,R9,R8,R4,R3";"R_Axial_DIN0411_L9.9mm_D3.6mm_P15.24mm_Horizontal";5;"30k";;;
21;"R5,R1";"R_Axial_DIN0411_L9.9mm_D3.6mm_P15.24mm_Horizontal";2;"62k";;;
22;"Q1";"TO-92_Inline";1;"BC547";;;
23;"LS1";"PinHeader_1x02_P2.54mm_Vertical";1;"Speaker";;;
24;"J1";"PinHeader_1x02_P2.54mm_Vertical";1;"Conn_01x02_Male";;;
25;"CP4,CP2";"CP_Radial_D10.0mm_P5.00mm";2;"C";;;
26;"CP3,CP1,C6,C2";"CP_Radial_D10.0mm_P5.00mm";4;"1uf";;;
27;"C11";"CP_Radial_D10.0mm_P5.00mm";1;"10nf";;;
28;"C9,C7";"CP_Radial_D10.0mm_P5.00mm";2;".1uF";;;
29;"C8";"CP_Radial_D10.0mm_P5.00mm";1;"10uf";;;
30;"C3";"CP_Radial_D14.0mm_P7.50mm";1;"250uf";;;
31;"C1";"CP_Radial_D14.0mm_P7.50mm";1;"10uF";;;
